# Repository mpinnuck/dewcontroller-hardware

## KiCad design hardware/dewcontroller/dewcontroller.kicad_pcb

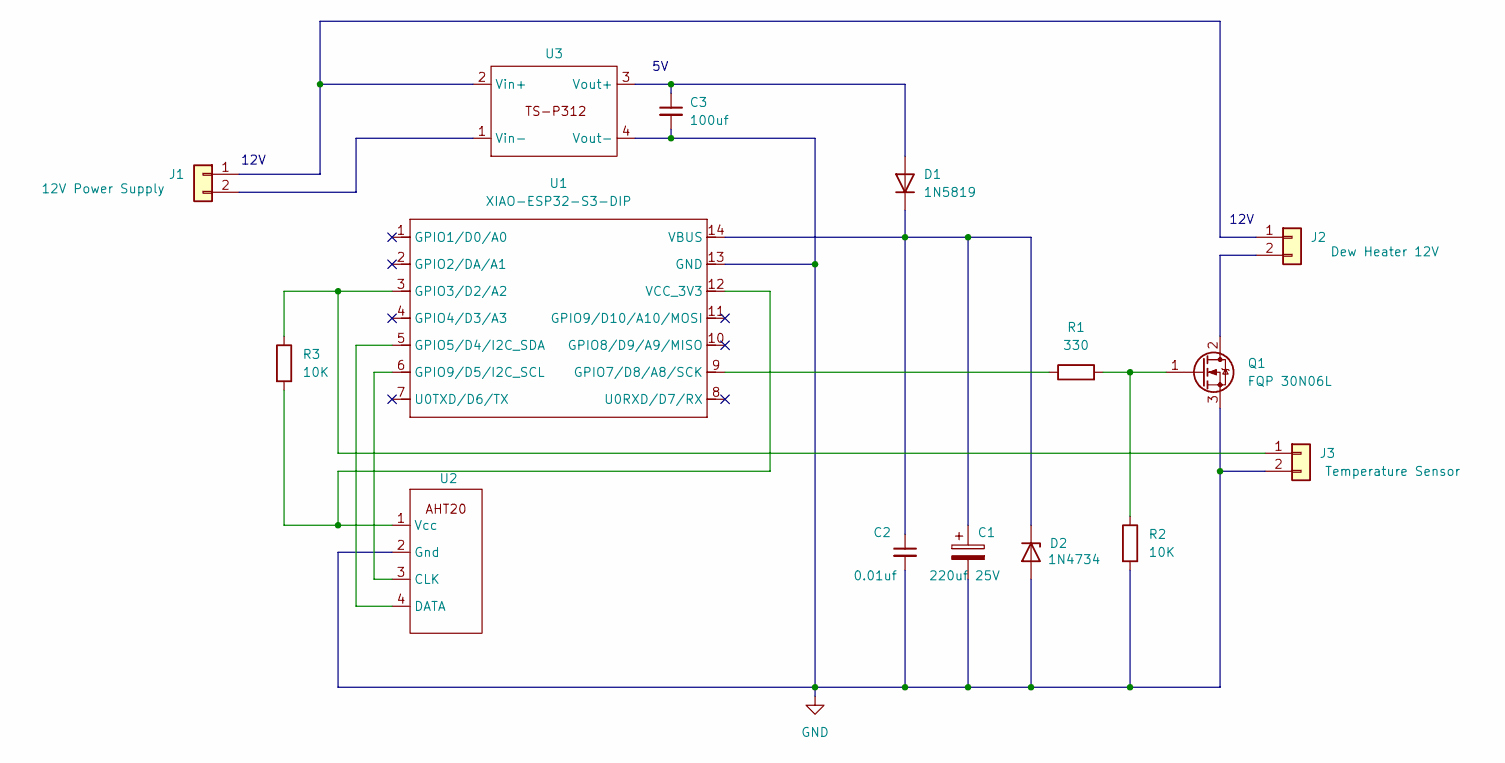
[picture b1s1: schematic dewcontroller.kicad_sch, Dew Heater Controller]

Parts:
C1: 220uf 25V; CP_Radial_D5.0mm_P2.00mm
C2: 0.01uf; C_Disc_D3.0mm_W1.6mm_P2.50mm
C3: 100uf; CP_Radial_D5.0mm_P2.00mm
D1: 1N5819; D_DO-41_SOD81_P7.62mm_Horizontal
D2: 1N4734; D_DO-41_SOD81_P7.62mm_Horizontal
J1: 12V Power Supply; JST_XH_B2B-XH-A_1x02_P2.50mm_Vertical
J2: Dew Heater 12V; JST_XH_B2B-XH-A_1x02_P2.50mm_Vertical
J3: Temperature Sensor; JST_XH_B2B-XH-A_1x02_P2.50mm_Vertical
Q1: FQP 30N06L; TO-220-3_Vertical
R1: 330; R_Axial_DIN0207_L6.3mm_D2.5mm_P10.16mm_Horizontal
R2, R3: 10K; R_Axial_DIN0207_L6.3mm_D2.5mm_P10.16mm_Horizontal
U1: XIAO-ESP32-S3-DIP; MCU_Seeed_ESP32C3_EdgeOnly
U2: AHT20
U3: Converter TS-P312 DC Buck

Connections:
GND: C1.2, C2.2, C3.2, D2.2 (A), J3.2, Q1.3 (S), R2.2, U1.13 (GND), U2.2 (Gnd), U3.4 (Vout-)
unnamed: C3.1, D1.2 (A), U3.3 (Vout+)
unnamed: C1.1, C2.1, D1.1 (K), D2.1 (K), U1.14 (VBUS)
unnamed: J1.1, J2.1 (12V), U3.2 (Vin+)
unnamed: J1.2, U3.1 (Vin-)
unnamed: J2.2 (Gnd), Q1.2 (D)
unnamed: J3.1, R3.1, U1.3 (GPIO3/D2/A2)
unnamed: Q1.1 (G), R1.2, R2.1
unnamed: U1.5 (GPIO5/D4/I2C_SDA), U2.4 (DATA)
unnamed: R1.1, U1.9 (GPIO7/D8/A8/SCK)
unnamed: U1.6 (GPIO9/D5/I2C_SCL), U2.3 (CLK)
unnamed: R3.2, U1.12 (VCC_3V3), U2.1 (Vcc)

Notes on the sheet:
12V

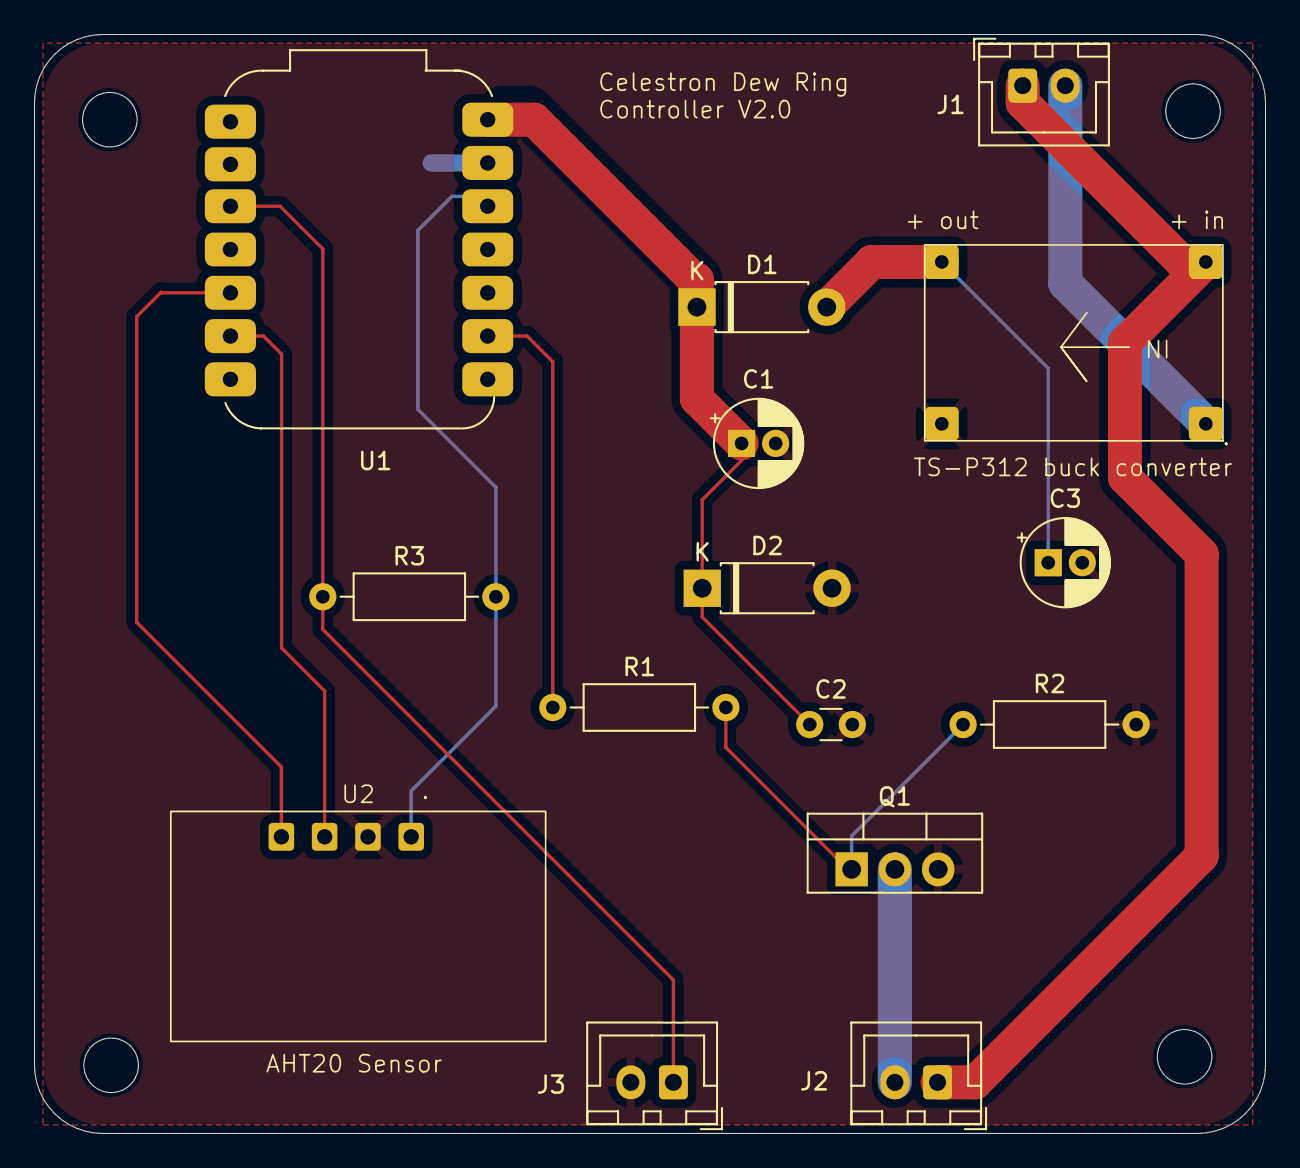
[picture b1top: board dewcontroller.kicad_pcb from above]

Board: 2 copper layers, 72.3 x 64.5 mm, 15 parts (0 on the bottom side), 12 nets.

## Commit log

2025-05-25 v1.0 firmware
2025-05-25 v1.0 pinout
2025-05-25 v2 firmware
2025-05-28 V3 Initial production version
2025-05-28 v3.1 test sketches
2025-05-28 V3.2 turned led on when wifi connected
2025-06-08 v3.3. add LED control
2025-06-08 V3.4 Added timezone
2025-06-08 V3.4 mechanical and electrical
2025-06-08 v3.5 gitignore
2025-06-09 v3.5 add clear data, calibration continues until stopped more data
2025-06-10 v3.6 added new calibration strategy and version number
2025-06-10 v4 added wifi lost recovery in loop()
2025-06-11 V2 - added weather station and SHT40 sensor
2025-06-12 v2.1 toggle heater button text
2025-06-12 v2.2 improved heating algorithm
2025-06-12 v2.3 added Proportional Integration (PI) controller logic
2025-07-05 v2.4 in progress
2025-07-05 V2.4d latest thermistor ambient temp data
2025-07-06 V2.5 has ambient gradient logging firts full functioning version
2025-09-09 V2.6 dewspread of 3 triggers heater, not rh 80%
2025-11-12 v2.7 Improved wifi connection managment
2025-11-13 v2.7.1 added background thread for long running tasks.
2025-11-13 v2.7.2 browser connection recovery improvements
2025-11-14 v2.7.3 removed Tg lag logging
2025-11-20 V2.7.4 tidy up background task and config corruption
2025-11-24 v2.7.5 If no Wifi credentials go straight to AP mode. If Wifi credentials change reboot
2025-12-18 v2.8.0 default sensor now AHT20 matches what is on the board
2025-12-29 v2.9.0 add SOURCE_WEATHER as fallback if SHT40 fails to initialize
2026-03-22 V2.9.0a kicad update
2026-03-22 v3.0.0 fixed AP fallback
2026-04-04 V4.0.0 made thread safe, improved gheating algorithm fixed bugs
2026-04-12 v4.1.0 fixed STA mode check in AP mode
2026-04-13 V4.2.0 added thermal log and show log data now pops up data panel
2026-04-14 v4.3.0 removed thermal data logging from UI now to persistant storage.
2026-04-19 V4.4.0 added additional columns to thermal log, removed redundant UI functions
2026-04-22 v4.5.0 added date tim eto status.json
2026-05-12 Ignore KiCad lock files and .history directory
2026-05-12 v5.0.0 chaged heating algorithm to a spread table
2026-05-13 v5.1.0 upated dewtable, change to light theme
